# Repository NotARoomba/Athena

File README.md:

<h1 align="center">
  <br>
  
  <br>
  Athena
  <br>
</h1>

<h4 align="center">
Advanced Flight Computer with Triple MCU Architecture

</h4>

<div align="center">

</div>

<p align="center">
  <a href="#key-features">Key Features</a> •
  <a href="#board-overview">Board Overview</a> •
  <a href="#specifications">Specifications</a> •
  <a href="#components">Components</a> •
  <a href="#credits">Credits</a> •
  <a href="#license">License</a>
</p>

## Key Features

- **Triple MCU Architecture**: STM32H753VIT6 (MPU), STM32H743VIT6 (TPU), STM32G474RET6 (SPU)
- **6 Pyro Channels**: Direct 12V battery connection with fuse protection
- **6 PWM Channels**: 2 for TVC (Thrust Vector Control), 4 for fin control
- **Advanced Sensors**: Triple ICM-45686 IMUs, LIS2MDLTR magnetometer, ICP-20100 & BMP388 barometers
- **GNSS & Communication**: NEO-M8U-06B GPS, LoRa RA-02 telemetry, Bluetooth DA14531MOD
- **Storage**: SD Card + Winbond W25Q256JV flash memory
- **Power Management**: 7.4-12V LiPo battery with BQ25713 charger, TPS25751 USB-C PD controller
- **6-Layer PCB**: Dedicated power planes and signal routing

## Board Overview

Athena is a high-performance flight computer designed for advanced rocketry applications. The board features a sophisticated 6-layer PCB design with dedicated power planes and optimized signal routing.

### Board Images

### PCB Design Process

The board was designed in EasyEDA with careful attention to power distribution and signal integrity:

## Specifications

### Physical Specifications

- **Board Size**: 80mm × 140mm
- **Layer Count**: 6 layers
- **Thickness**: Standard PCB thickness
- **Connectors**: USB-C, SD Card slot, various headers

### Power Specifications

- **Input Voltage**: 7.4V LiPo battery
- **Regulated Outputs**: 5V, 3.3V
- **Charging**: USB-C Power Delivery support

### Communication Interfaces

- **GNSS**: NEO-M8U-06B GPS module
- **LoRa**: RA-02 for long-range telemetry
- **Bluetooth**: DA14531MOD for local communication
- **CAN**: TCAN1057AVDRQ1 transceiver
- **USB**: TUSB2036 USB hub
- **UART**: Dedicated UART channels for each STM with ESD protection

## Components

### Microcontrollers

- **MPU (Main Processing Unit)**: STM32H753VIT6 - Handles sensors and Kalman filtering
- **TPU (Telemetry Processing Unit)**: STM32H743VIT6 - Manages LoRa, SD card, and flash memory
- **SPU (Servo Processing Unit)**: STM32G474RET6 - Controls pyro channels and PWM outputs

### Sensors

- **IMU**: 3× ICM-45686 (triple redundancy)
- **Magnetometer**: LIS2MDLTR
- **Barometers**: ICP-20100, BMP388 (dual redundancy)

### Power Management

- **Battery Charger**: BQ25713RSNR (on the TPS25751's I2C controller bus)
- **USB-C PD Controller**: TPS25751DREFR (patched over I2C by the SPU at power-up)
- **Buck Converters**: LM5145RGYR (servo), TPS5430 (3.3V)

### Storage & Communication

- **Flash Memory**: Winbond W25Q256JV
- **SD Card**: Standard microSD slot
- **GPS**: NEO-M8U-06B
- **LoRa**: RA-02
- **Bluetooth**: DA14531MOD-00F01002

## Dashboard

[docs/](docs/) is the built dashboard (source in [software/web](software/web): React 19 + Vite +
Tailwind + recharts + three.js, same stack as [cyberboard.notaroomba.dev](https://cyberboard.notaroomba.dev)),
served at [athena.notaroomba.dev](https://athena.notaroomba.dev) by GitHub Pages. It shows the 3D
attitude, accel/gyro/altitude charts, flight flags, GPS, a live **ground-track map** (filter
estimate, dead-reckoned stretches dashed, raw GPS, landing estimate from the current descent,
distance/bearing from the pad, apogee and max speed), and the SPU **recovery & power** panel
(flight phase, arming, the six pyro channels, battery/charger/USB-PD state) with ARM / DISARM /
FIRE / servo / main-altitude commands when a writable link is open, a **flight event timeline**
(launch, phases, pyro firings, arming) with a summary line (apogee, max speed, max g, flight time,
landing distance), per-type frame rates, a **REC** button that saves the raw link stream as a
replayable `.bin`, a **REPORT** button that downloads a JSON flight report (summary, events, tracks, last
frames, console), a **pre-flight checklist** (GO/NO-GO read from the live data: IMUs, baro, GPS fix,
pad origin, SPU link, main altitude, radio, arming, plus a hand-ticked list), **SOUND** alerts on
launch/apogee/pyro/landing, a **T-60 countdown** (beeps over the last 10 s, cancels itself at launch), a no-data
banner, the altitude and phase in the tab title, a metres/feet display toggle, and keyboard shortcuts (`d` demo, `t` countdown, `c` checklist,
`s` sound, `l` login, `r` record). Data sources:

- **SERIAL**: any of the three USB ports (WebSerial, Chrome/Edge over https or localhost).
- **BLUETOOTH**: the DA14531 on the TPU over Web Bluetooth (DSPS serial-bridge firmware streams the
  telemetry; the factory CodeLess firmware only answers AT commands).
- **REPLAY**: an `ATHnnnnn.BIN` from the SD card, a flash dump, a dashboard recording or a ground-station
  log, paced by its own timestamps, with a speed selector, pause (space) and a seek bar.
- **DEMO**: a scripted flight (with a GPS dropout) through the real encoder/decoder.
- viewers: an admin's serial/Bluetooth bytes (or a ground station's) are relayed through the WebSocket
  server in [software/server](software/server) (axum, on Railway at `api.athena.notaroomba.dev`). A logged-in
  viewer can also send commands: the server hands them to the connected ground station, which writes them
  to its uplink port, and reports whether anyone was there to carry them.

Locally: `cd software/web && npm install && npm run dev` (or `python3 -m http.server 8787 --directory docs`).

## Firmware

Three CubeMX projects (`firmware/MPU`, `firmware/TPU`, `firmware/SPU`) share the pure-C
modules in `firmware/Athena`: the inter-MCU/LoRa framing (`athena_link`), the UBX parser
(`ubx`), the navigation filter (`fusion`: Mahony attitude + per-axis Kalman filters with
IMU dead reckoning, barometer and GPS corrections) and the SPU recovery logic (`recovery`:
flight phase from the fused state, drogue at apogee, main below a set altitude, servo outputs).
`cd firmware && make debug` builds all three (`brew install osx-cross/arm/arm-gcc-bin@14` for the
toolchain) and `make host-test` runs the PC self-check of the shared modules including a scripted
flight through the recovery logic.

`./firmware/flash.sh` flashes over USB DFU with `dfu-util` and tells the MCUs apart by USB hub
port. No buttons are needed: `B` on any MCU's USB console disconnects USB, leaves a magic word in
RAM and resets into the ST ROM bootloader (`J` jumps in place as a fallback); the script does this
itself. After reset each MCU shows its identity colour for 3 s: **MPU green, TPU red, SPU blue**.

Links: MPU -> TPU (UART4/UART8, state 20 Hz, GPS back), MPU -> SPU (UART8/UART5, state 20 Hz,
SPU status 2 Hz back), TPU -> MPU -> SPU for commands (LoRa uplink, USB, Bluetooth). The TPU
logs every link frame to the microSD card (one `ATHnnnnn.BIN` per boot, card hot-plug safe) and
to the W25Q256 flash, sends telemetry + SPU status over LoRa and over UART7 to the Bluetooth module;
`tools/athlog.py` dumps the flash log over USB and converts logs to CSV.

**Ground station on an RTL-SDR** (`tools/lora_rx.py`, macOS/Linux/Windows): a complete LoRa receiver for
the downlink (SF7, 125 kHz, sync 0x12) written in numpy, no GNU Radio, about 15% of one core at the
dongle's native 1 MS/s. It decodes the Athena frames straight from the IQ stream (the frames' own CRCs
verified 92% of packets on the bench), logs them to a replayable `athena-lora-*.bin`, and by default opens
the web dashboard fed live by this process (it serves `docs/` and speaks the relay protocol on
`ws://localhost:3001/ws`, including a `station` message with signal level, carrier offset and packet
counts that the dashboard shows in its footer, and its own log lines as TEXT frames so they appear in the
dashboard console; through `--relay` the public site gets both as well). `--app` opens it as a desktop window (pywebview) instead of
a browser tab, `--gain auto` uses the tuner AGC (the dongle is retried every 3 s when busy or unplugged),
`--uplink /dev/tty...` adds a command path (the rocket's USB console on the bench, or a TPU
in ground-station mode: `G` on its console turns a second board into a LoRa<->USB relay), `--tui` gives a
terminal UI, `--relay wss://api.athena.notaroomba.dev/ws --password ...` also feeds the public site and
accepts commands from it, `--file cap.cu8` replays a capture. Needs `pip install numpy scipy websockets
websocket-client pyserial pywebview` and `rtl_sdr` (`brew install librtlsdr`). `tools/build_station.sh` packs
it into one standalone executable (`dist/station/athena-station`, PyInstaller, dashboard files included) so a
laptop at the range only needs `rtl_sdr` installed; the `station` GitHub Actions workflow builds it for
macOS, Windows and Linux (run it from the Actions tab or push a `v*` tag, then download the artifact).
`tools/lora_check.py` is the quick PHY check (burst period,
preamble, sync word).

USB console characters: all MCUs `B`/`J` (DFU), `L` LEDs off/on; TPU `D` dump flash log, `E` restart it,
`S` sync SD, `F` format SD, `G` ground-station mode (persistent); SPU `A` arm, `d` disarm, `1`-`6` fire a
channel (armed only), `s` sweep servo 1, `r` reset the MPU. Pyros only get power when the external ARM terminal is closed.

## Credits

This project uses:

- [EasyEDA](https://easyeda.com/) - PCB design and schematic capture
- [STM32 HAL](https://www.st.com/en/embedded-software/stm32cube-hal.html) - Hardware abstraction layer
- [JLCPCB](https://jlcpcb.com/) - PCB manufacturing and assembly
- [Figma](https://figma.com/) - Silkscreen design

## You may also like...

- [Niveles De Niveles](https://github.com/NotARoomba/NivelesDeNiveles) – Real-time flood alert app
- [Linea](https://github.com/NotARoomba/Linea) – An EMR tablet
- [Tamaki](https://github.com/NotARoomba/Tamaki) – A cute HackPad

## License

MIT

---

> [notaroomba.dev](https://notaroomba.dev) &nbsp;&middot;&nbsp;
> GitHub [@NotARoomba](https://github.com/NotARoomba)

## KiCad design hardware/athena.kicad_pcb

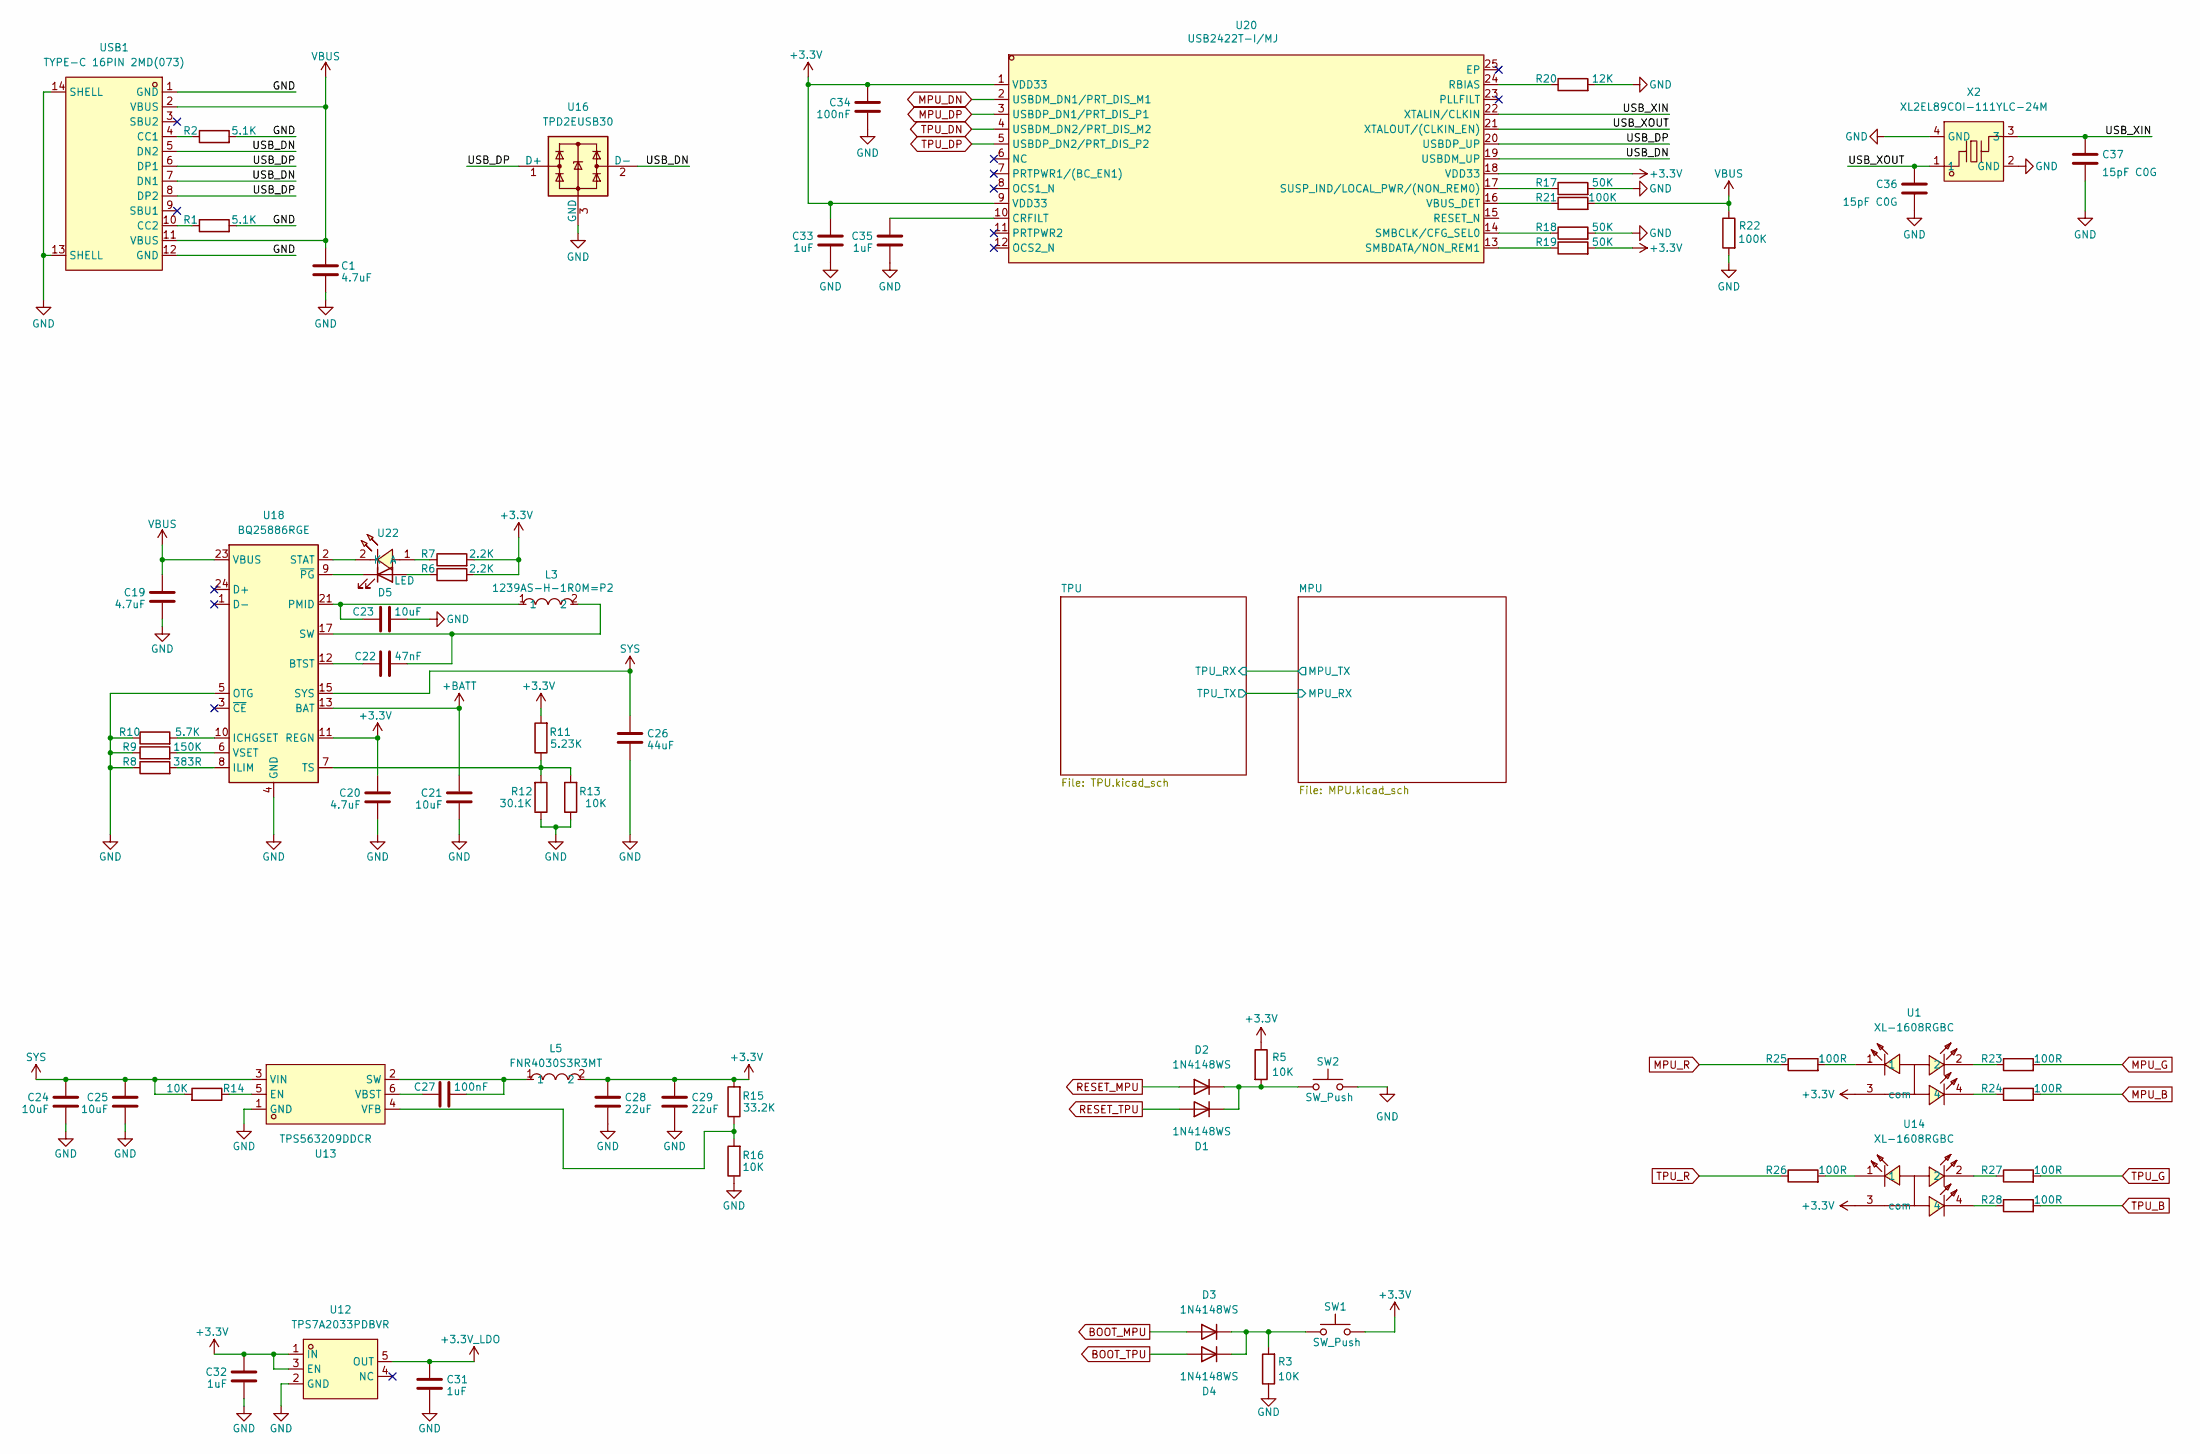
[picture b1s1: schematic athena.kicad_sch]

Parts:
C1, C19, C20: 4.7uF; C_0603_1608Metric
C21, C23, C24, C25: 10uF; C_0603_1608Metric
C22: 47nF; C_0402_1005Metric
C26: 44uF; C_0805_2012Metric
C27: 100nF; C_0402_1005Metric
C28, C29: 22uF; C_0805_2012Metric
C31, C32, C33, C35: 1uF; C_0402_1005Metric_Pad0.74x0.62mm_HandSolder
C34: 100nF; C_0402_1005Metric_Pad0.74x0.62mm_HandSolder
C36, C37: 15pF C0G; C_0402_1005Metric_Pad0.74x0.62mm_HandSolder
D1, D2, D3, D4: 1N4148WS; D_SOD-323
D5: LED; LED_0402_1005Metric; LCSC C52125197
L3: 1239AS-H-1R0M=P2; L1008; MPN 1239AS-H-1R0M=P2; LCSC Part C167447
L5: FNR4030S3R3MT; IND-SMD_L4.0-W4.0_FNR40XXS; MPN FNR4030S3R3MT; LCSC Part C167870
R1, R2: 5.1K; R_0402_1005Metric
R3, R5, R13, R14, R16: 10K; R_0402_1005Metric
R6, R7: 2.2K; R_0402_1005Metric
R8: 383R; R_0402_1005Metric
R9: 150K; R_0402_1005Metric
R10: 5.7K; R_0402_1005Metric
R11: 5.23K; R_0402_1005Metric
R12: 30.1K; R_0402_1005Metric
R15: 33.2K; R_0402_1005Metric
R17, R18, R19: 50K; R_0402_1005Metric
R20: 12K; R_0402_1005Metric
R21, R22: 100K; R_0402_1005Metric
R23, R24, R25, R26, R27, R28: 100R; R_0402_1005Metric
SW1, SW2: SW_Push; SW-SMD_L3.9-W3.0-P4.45; LCSC C720477
U1, U14: XL-1608RGBC; LED-SMD_4P-L1.6-W0.8-BL; MPN XL-1608RGBC; LCSC Part C5349936
U12: TPS7A2033PDBVR; SOT-23-5_L2.9-W1.6-P0.95-LS2.8-BR; LCSC Part C2862740
U13: TPS563209DDCR; SOT-23-6_L2.9-W1.6-P0.95-LS2.8-BR; LCSC Part C181974
U16: TPD2EUSB30; Texas_DRT-3
U18: BQ25886RGE; Texas_RGE0024H_VQFN-24-1EP_4x4mm_P0.5mm_EP2.7x2.7mm
U20: USB2422T-I/MJ; QFN-24_L4.0-W4.0-P0.50-TL-EP2.5; LCSC Part C622610
U22: SZYY0402Y_C434450; LED0402-FD_YELLOW; LCSC Part C434450
USB1: TYPE-C 16PIN 2MD(073); USB-C-SMD_TYPE-C-6PIN-2MD-073; LCSC Part C2765186
X2: XL2EL89COI-111YLC-24M; CRYSTAL-SMD_4P-L3.2-W2.5-BL; MPN XL2EL89COI-111YLC-24M; LCSC Part C5444545

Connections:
+3.3V: C20.1, C28.1, C29.1, C32.1, C33.1, C34.1, L5.2, R5.1, R6.2, R7.2, R11.2, R15.2, R19.2, SW1.2, U1.3 (com), U12.1 (IN), U12.3 (EN), U14.3 (com), U18.11 (REGN), U20.1 (VDD33), U20.9 (VDD33), U20.18 (VDD33); also elsewhere on the board
+3.3V_LDO: C31.1, U12.5 (OUT); also elsewhere on the board
+BATT: C21.1, U18.13 (BAT), U18.14 (BAT)
/USB_DN: U16.2 (D-), U20.19 (USBDM_UP), USB1.5 (DN2), USB1.7 (DN1)
/USB_DP: U16.1 (D+), U20.20 (USBDP_UP), USB1.6 (DP1), USB1.8 (DP2)
/USB_XIN: C37.1, U20.22 (XTALIN/CLKIN), X2.3
/USB_XOUT: C36.1, U20.21 (XTALOUT/(CLKIN_EN)), X2.1
BOOT_MPU: D3.2 (A); also elsewhere on the board
BOOT_TPU: D4.2 (A); also elsewhere on the board
GND: C1.2, C19.2, C20.2, C21.2, C23.2, C24.2, C25.2, C26.2, C28.2, C29.2, C31.2, C32.2, C33.2, C34.2, C35.2, C36.2, C37.2, R1.2, R2.2, R3.1, R8.1, R9.1, R10.1, R12.1, R13.1, R16.1, R17.2, R18.2, R20.2, R22.2, SW2.2, U12.2 (GND), U13.1 (GND), U16.3 (GND), U18.4 (GND), U18.5 (OTG), U18.19 (GND), U18.20 (GND), U18.25 (GND), USB1.1 (GND), USB1.12 (GND), USB1.13 (SHELL), USB1.14 (SHELL), X2.2 (GND), X2.4 (GND); also elsewhere on the board
MPU_B: R24.2; also elsewhere on the board
MPU_DN: U20.2 (USBDM_DN1/PRT_DIS_M1); also elsewhere on the board
MPU_DP: U20.3 (USBDP_DN1/PRT_DIS_P1); also elsewhere on the board
MPU_G: R23.2; also elsewhere on the board
MPU_R: R25.1; also elsewhere on the board
unnamed: C22.1, L3.2, U18.17 (SW), U18.18 (SW)
unnamed: C23.1, L3.1, U18.21 (PMID), U18.22 (PMID)
unnamed: D1.1 (K), D2.1 (K), R5.2, SW2.1
unnamed: D3.1 (K), D4.1 (K), R3.2, SW1.1
unnamed: D5.2 (A), R6.1
unnamed: D5.1 (K), U18.9 (~PG)
unnamed: R23.1, U1.2
unnamed: R24.1, U1.4
unnamed: R25.2, U1.1
unnamed: R26.2, U14.1
unnamed: R27.1, U14.2
unnamed: R28.1, U14.4
unnamed: R14.1, U13.5 (EN)
unnamed: C27.1, L5.1, U13.2 (SW)
unnamed: C27.2, U13.6 (VBST)
unnamed: R15.1, R16.2, U13.4 (VFB)
unnamed: C22.2, U18.12 (BTST)
unnamed: R10.2, U18.10 (ICHGSET)
unnamed: R8.2, U18.8 (ILIM)
unnamed: U18.2 (STAT), U22.2 (K)
unnamed: R11.1, R12.2, R13.2, U18.7 (TS)
unnamed: R9.2, U18.6 (VSET)
unnamed: C35.1, U20.10 (CRFILT)
unnamed: R20.1, U20.24 (RBIAS)
unnamed: R18.1, U20.14 (SMBCLK/CFG_SEL0)
unnamed: R19.1, U20.13 (SMBDATA/NON_REM1)
unnamed: R17.1, U20.17 (SUSP_IND/LOCAL_PWR/(NON_REM0))
unnamed: R21.1, U20.16 (VBUS_DET)
unnamed: R7.1, U22.1 (A)
unnamed: R2.1, USB1.4 (CC1)
unnamed: R1.1, USB1.10 (CC2)
RESET_MPU: D2.2 (A); also elsewhere on the board
RESET_TPU: D1.2 (A); also elsewhere on the board
SYS: C24.1, C25.1, C26.1, R14.2, U13.3 (VIN), U18.15 (SYS), U18.16 (SYS)
TPU_B: R28.2; also elsewhere on the board
TPU_DN: U20.4 (USBDM_DN2/PRT_DIS_M2); also elsewhere on the board
TPU_DP: U20.5 (USBDP_DN2/PRT_DIS_P2); also elsewhere on the board
TPU_G: R27.2; also elsewhere on the board
TPU_R: R26.1; also elsewhere on the board
VBUS: C1.1, C19.1, R21.2, R22.1, U18.23 (VBUS), USB1.2 (VBUS), USB1.11 (VBUS)

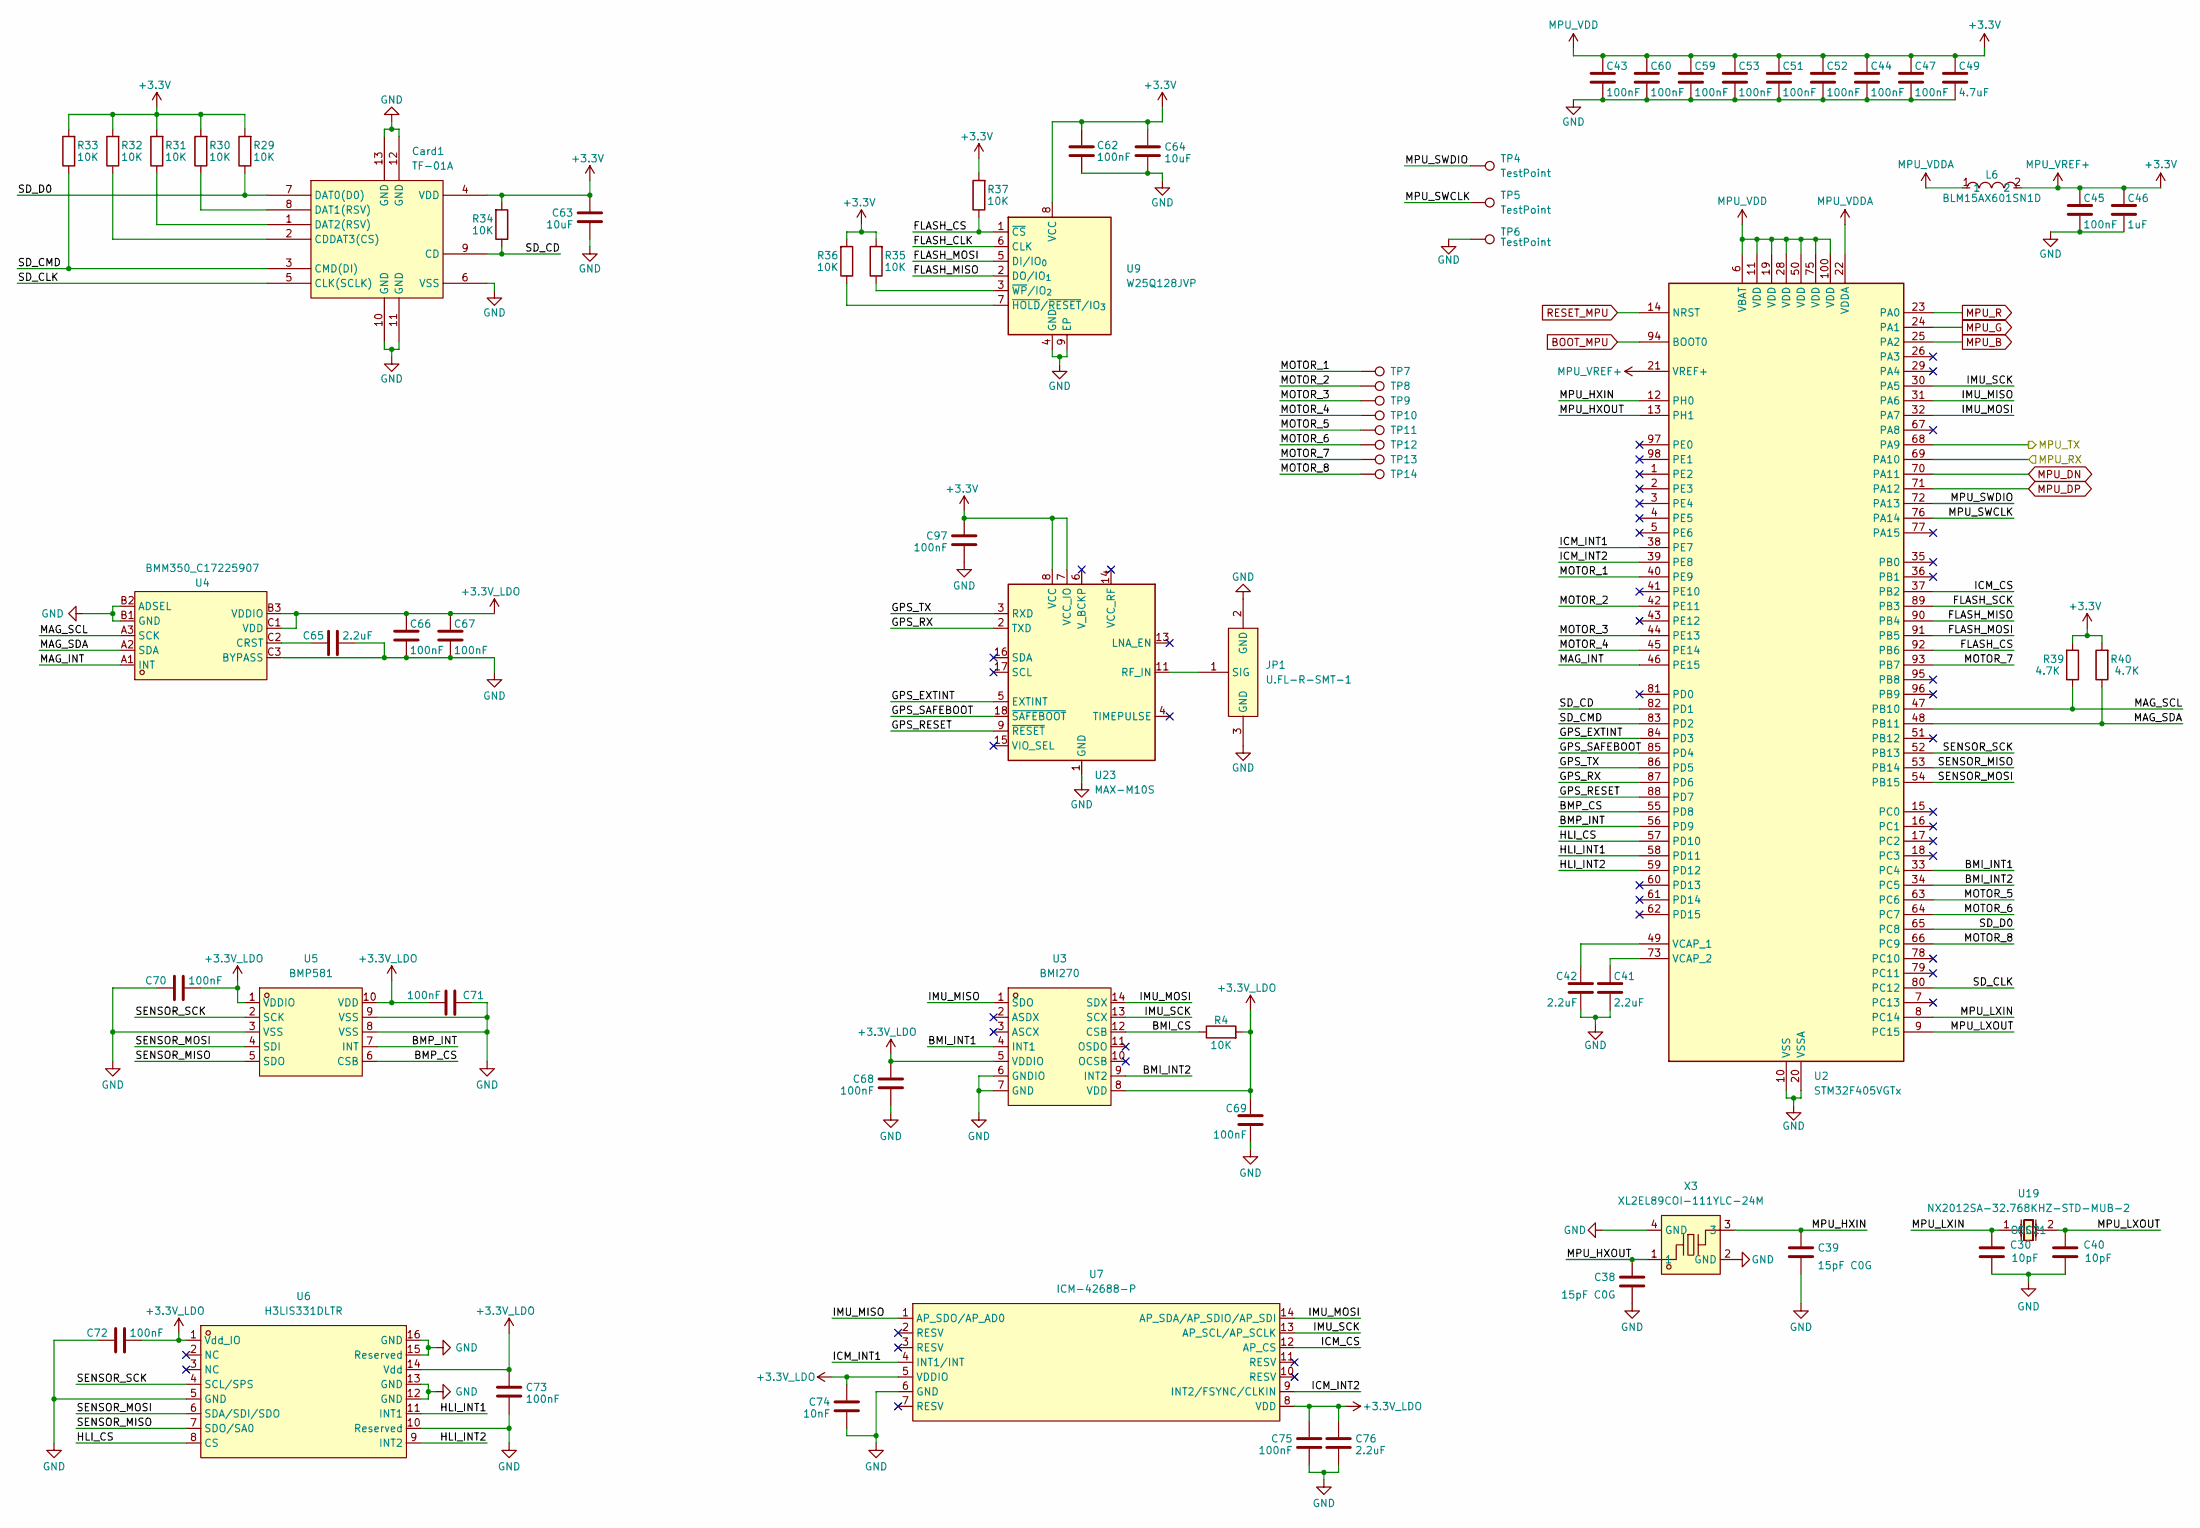
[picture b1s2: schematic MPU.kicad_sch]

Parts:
C30, C40: 10pF; C_0402_1005Metric
C38, C39: 15pF C0G; C_0402_1005Metric_Pad0.74x0.62mm_HandSolder
C41, C42, C65, C76: 2.2uF; C_0402_1005Metric
C43, C44, C45, C47, C51, C52, C53, C59, C60, C62, C66, C67, C68, C69, C70, C71, C72, C73, C75, C97: 100nF; C_0402_1005Metric
C46: 1uF; C_0402_1005Metric
C49: 4.7uF; C_0603_1608Metric
C63, C64: 10uF; C_0603_1608Metric
C74: 10nF; C_0402_1005Metric
Card1: TF-01A; TF-SMD_TF-01A; LCSC Part C91145
JP1: U.FL-R-SMT-1; RF-SMD_FRF05002-JSS103M; MPN U.FL-R-SMT-1(80); LCSC Part C88374
L6: BLM15AX601SN1D; L0402; MPN BLM15AX601SN1D; LCSC Part C76886
R4, R29, R30, R31, R32, R33, R34, R35, R36, R37: 10K; R_0402_1005Metric
R39, R40: 4.7K; R_0402_1005Metric
TP4, TP5, TP6: TestPoint; TestPoint_Pad_1.0x1.0mm
TP7, TP8, TP9, TP10, TP11, TP12, TP13, TP14: TestPoint; TestPoint_Pill
U2: STM32F405VGTx; LQFP-100_14x14mm_P0.5mm
U3: BMI270; LGA-14_L3.0-W2.5-P0.50-BR; LCSC Part C2836813
U4: BMM350_C17225907; WLCSP-9_L1.3-W1.3-R3-C3-P0.40-TL; LCSC Part C17225907
U5: BMP581; LGA-10_L2.0-W2.0-P0.50-TL_BMP581; LCSC Part C5362283
U6: H3LIS331DLTR; LGA-16_L3.0-W3.0-P0.50-BL; LCSC Part C2655074
U7: ICM-42688-P; LGA-14_L3.0-W2.5-P0.50-TL; LCSC Part C1850418
U9: W25Q128JVP; WSON-8-1EP_6x5mm_P1.27mm_EP3.4x4.3mm
U19: NX2012SA-32.768KHZ-STD-MUB-2; CRYSTAL-SMD_L2.0-W1.2; LCSC Part C891748
U23: MAX-M10S; ublox_MAX
X3: XL2EL89COI-111YLC-24M; CRYSTAL-SMD_4P-L3.2-W2.5-BL; MPN XL2EL89COI-111YLC-24M; LCSC Part C5444545

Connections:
+3.3V: C43.1, C44.1, C45.1, C46.1, C47.1, C49.1, C51.1, C52.1, C53.1, C59.1, C60.1, C62.1, C63.1, C64.1, C97.1, Card1.4 (VDD), L6.2, R29.2, R30.2, R31.2, R32.2, R33.2, R34.2, R35.2, R36.2, R37.2, R39.2, R40.2, U2.6 (VBAT), U2.11 (VDD), U2.19 (VDD), U2.21 (VREF+), U2.28 (VDD), U2.50 (VDD), U2.75 (VDD), U2.100 (VDD), U9.8 (VCC), U23.7 (VCC_IO), U23.8 (VCC); also elsewhere on the board
+3.3V_LDO: C66.1, C67.1, C68.1, C69.1, C70.2, C71.2, C72.2, C73.1, C74.1, C75.1, C76.1, R4.2, U3.5 (VDDIO), U3.8 (VDD), U4.B3 (VDDIO), U4.C1 (VDD), U5.1 (VDDIO), U5.10 (VDD), U6.1 (Vdd_IO), U6.14 (Vdd), U7.5 (VDDIO), U7.8 (VDD); also elsewhere on the board
/MPU/BMI_CS: R4.1, U3.12 (CSB)
/MPU/BMI_INT1: U2.33 (PC4), U3.4 (INT1)
/MPU/BMI_INT2: U2.34 (PC5), U3.9 (INT2)
/MPU/BMP_CS: U2.55 (PD8), U5.6 (CSB)
/MPU/BMP_INT: U2.56 (PD9), U5.7 (INT)
/MPU/FLASH_CLK: U9.6 (CLK)
/MPU/FLASH_CS: R37.1, U2.92 (PB6), U9.1 (~CS)
/MPU/FLASH_MISO: U2.90 (PB4), U9.2 (DO/IO_{1})
/MPU/FLASH_MOSI: U2.91 (PB5), U9.5 (DI/IO_{0})
/MPU/FLASH_SCK: U2.89 (PB3)
/MPU/GPS_EXTINT: U2.84 (PD3), U23.5 (EXTINT)
/MPU/GPS_RESET: U2.88 (PD7), U23.9 (~RESET)
/MPU/GPS_RX: U2.87 (PD6), U23.2 (TXD)
/MPU/GPS_SAFEBOOT: U2.85 (PD4), U23.18 (~SAFEBOOT)
/MPU/GPS_TX: U2.86 (PD5), U23.3 (RXD)
/MPU/HLI_CS: U2.57 (PD10), U6.8 (CS)
/MPU/HLI_INT1: U2.58 (PD11), U6.11 (INT1)
/MPU/HLI_INT2: U2.59 (PD12), U6.9 (INT2)
/MPU/ICM_CS: U2.37 (PB2), U7.12 (AP_CS)
/MPU/ICM_INT1: U2.38 (PE7), U7.4 (INT1/INT)
/MPU/ICM_INT2: U2.39 (PE8), U7.9 (INT2/FSYNC/CLKIN)
/MPU/IMU_MISO: U2.31 (PA6), U3.1 (SDO), U7.1 (AP_SDO/AP_AD0)
/MPU/IMU_MOSI: U2.32 (PA7), U3.14 (SDX), U7.14 (AP_SDA/AP_SDIO/AP_SDI)
/MPU/IMU_SCK: U2.30 (PA5), U3.13 (SCX), U7.13 (AP_SCL/AP_SCLK)
/MPU/MAG_INT: U2.46 (PE15), U4.A1 (INT)
/MPU/MAG_SCL: R39.1, U2.47 (PB10), U4.A3 (SCK)
/MPU/MAG_SDA: R40.1, U2.48 (PB11), U4.A2 (SDA)
/MPU/MOTOR_1: TP7.1 (1_1), U2.40 (PE9)
/MPU/MOTOR_2: TP8.1 (1_1), U2.42 (PE11)
/MPU/MOTOR_3: TP9.1 (1_1), U2.44 (PE13)
/MPU/MOTOR_4: TP10.1 (1_1), U2.45 (PE14)
/MPU/MOTOR_5: TP11.1 (1_1), U2.63 (PC6)
/MPU/MOTOR_6: TP12.1 (1_1), U2.64 (PC7)
/MPU/MOTOR_7: TP13.1 (1_1), U2.93 (PB7)
/MPU/MOTOR_8: TP14.1 (1_1), U2.66 (PC9)
/MPU/MPU_HXIN: C39.1, U2.12 (PH0), X3.3
/MPU/MPU_HXOUT: C38.1, U2.13 (PH1), X3.1
/MPU/MPU_LXIN: C30.1, U2.8 (PC14), U19.1 (OSC1)
/MPU/MPU_LXOUT: C40.1, U2.9 (PC15), U19.2 (OSC2)
/MPU/MPU_RX: U2.69 (PA10); also elsewhere on the board
/MPU/MPU_SWCLK: TP5.1 (1_1), U2.76 (PA14)
/MPU/MPU_SWDIO: TP4.1 (1_1), U2.72 (PA13)
/MPU/MPU_TX: U2.68 (PA9); also elsewhere on the board
/MPU/SD_CD: Card1.9 (CD), R34.1, U2.82 (PD1)
/MPU/SD_CLK: Card1.5 (CLK(SCLK)), U2.80 (PC12)
/MPU/SD_CMD: Card1.3 (CMD(DI)), R33.1, U2.83 (PD2)
/MPU/SD_D0: Card1.7 (DAT0(D0)), R29.1, U2.65 (PC8)
/MPU/SENSOR_MISO: U2.53 (PB14), U5.5 (SDO), U6.7 (SDO/SA0)
/MPU/SENSOR_MOSI: U2.54 (PB15), U5.4 (SDI), U6.6 (SDA/SDI/SDO)
/MPU/SENSOR_SCK: U2.52 (PB13), U5.2 (SCK), U6.4 (SCL/SPS)
BOOT_MPU: U2.94 (BOOT0); also elsewhere on the board
GND: C30.2, C38.2, C39.2, C40.2, C41.2, C42.2, C43.2, C44.2, C45.2, C46.2, C47.2, C49.2, C51.2, C52.2, C53.2, C59.2, C60.2, C62.2, C63.2, C64.2, C65.1, C66.2, C67.2, C68.2, C69.2, C70.1, C71.1, C72.1, C73.2, C74.2, C75.2, C76.2, C97.2, Card1.6 (VSS), Card1.10 (GND), Card1.11 (GND), Card1.12 (GND), Card1.13 (GND), JP1.2 (GND), JP1.3 (GND), TP6.1 (1_1), U2.10 (VSS), U2.20 (VSSA), U2.27 (VSS), U2.74 (VSS), U2.99 (VSS), U3.6 (GNDIO), U3.7 (GND), U4.B1 (GND), U4.B2 (ADSEL), U4.C3 (BYPASS), U5.3 (VSS), U5.8 (VSS), U5.9 (VSS), U6.5 (GND), U6.10 (Reserved), U6.12 (GND), U6.13 (GND), U6.15 (Reserved), U6.16 (GND), U7.6 (GND), U9.4 (GND), U9.9 (EP), U23.1 (GND), U23.10 (GND), U23.12 (GND), X3.2 (GND), X3.4 (GND); also elsewhere on the board
MPU_B: U2.25 (PA2); also elsewhere on the board
MPU_DN: U2.70 (PA11); also elsewhere on the board
MPU_DP: U2.71 (PA12); also elsewhere on the board
MPU_G: U2.24 (PA1); also elsewhere on the board
MPU_R: U2.23 (PA0); also elsewhere on the board
MPU_VDDA: L6.1, U2.22 (VDDA)
unnamed: Card1.2 (CDDAT3(CS)), R32.1
unnamed: Card1.8 (DAT1(RSV)), R30.1
unnamed: Card1.1 (DAT2(RSV)), R31.1
unnamed: JP1.1 (SIG), U23.11 (RF_IN)
unnamed: C42.1, U2.49 (VCAP_1)
unnamed: C41.1, U2.73 (VCAP_2)
unnamed: C65.2, U4.C2 (CRST)
unnamed: R36.1, U9.7 (~HOLD/~RESET/IO_{3})
unnamed: R35.1, U9.3 (~WP/IO_{2})
RESET_MPU: U2.14 (NRST); also elsewhere on the board

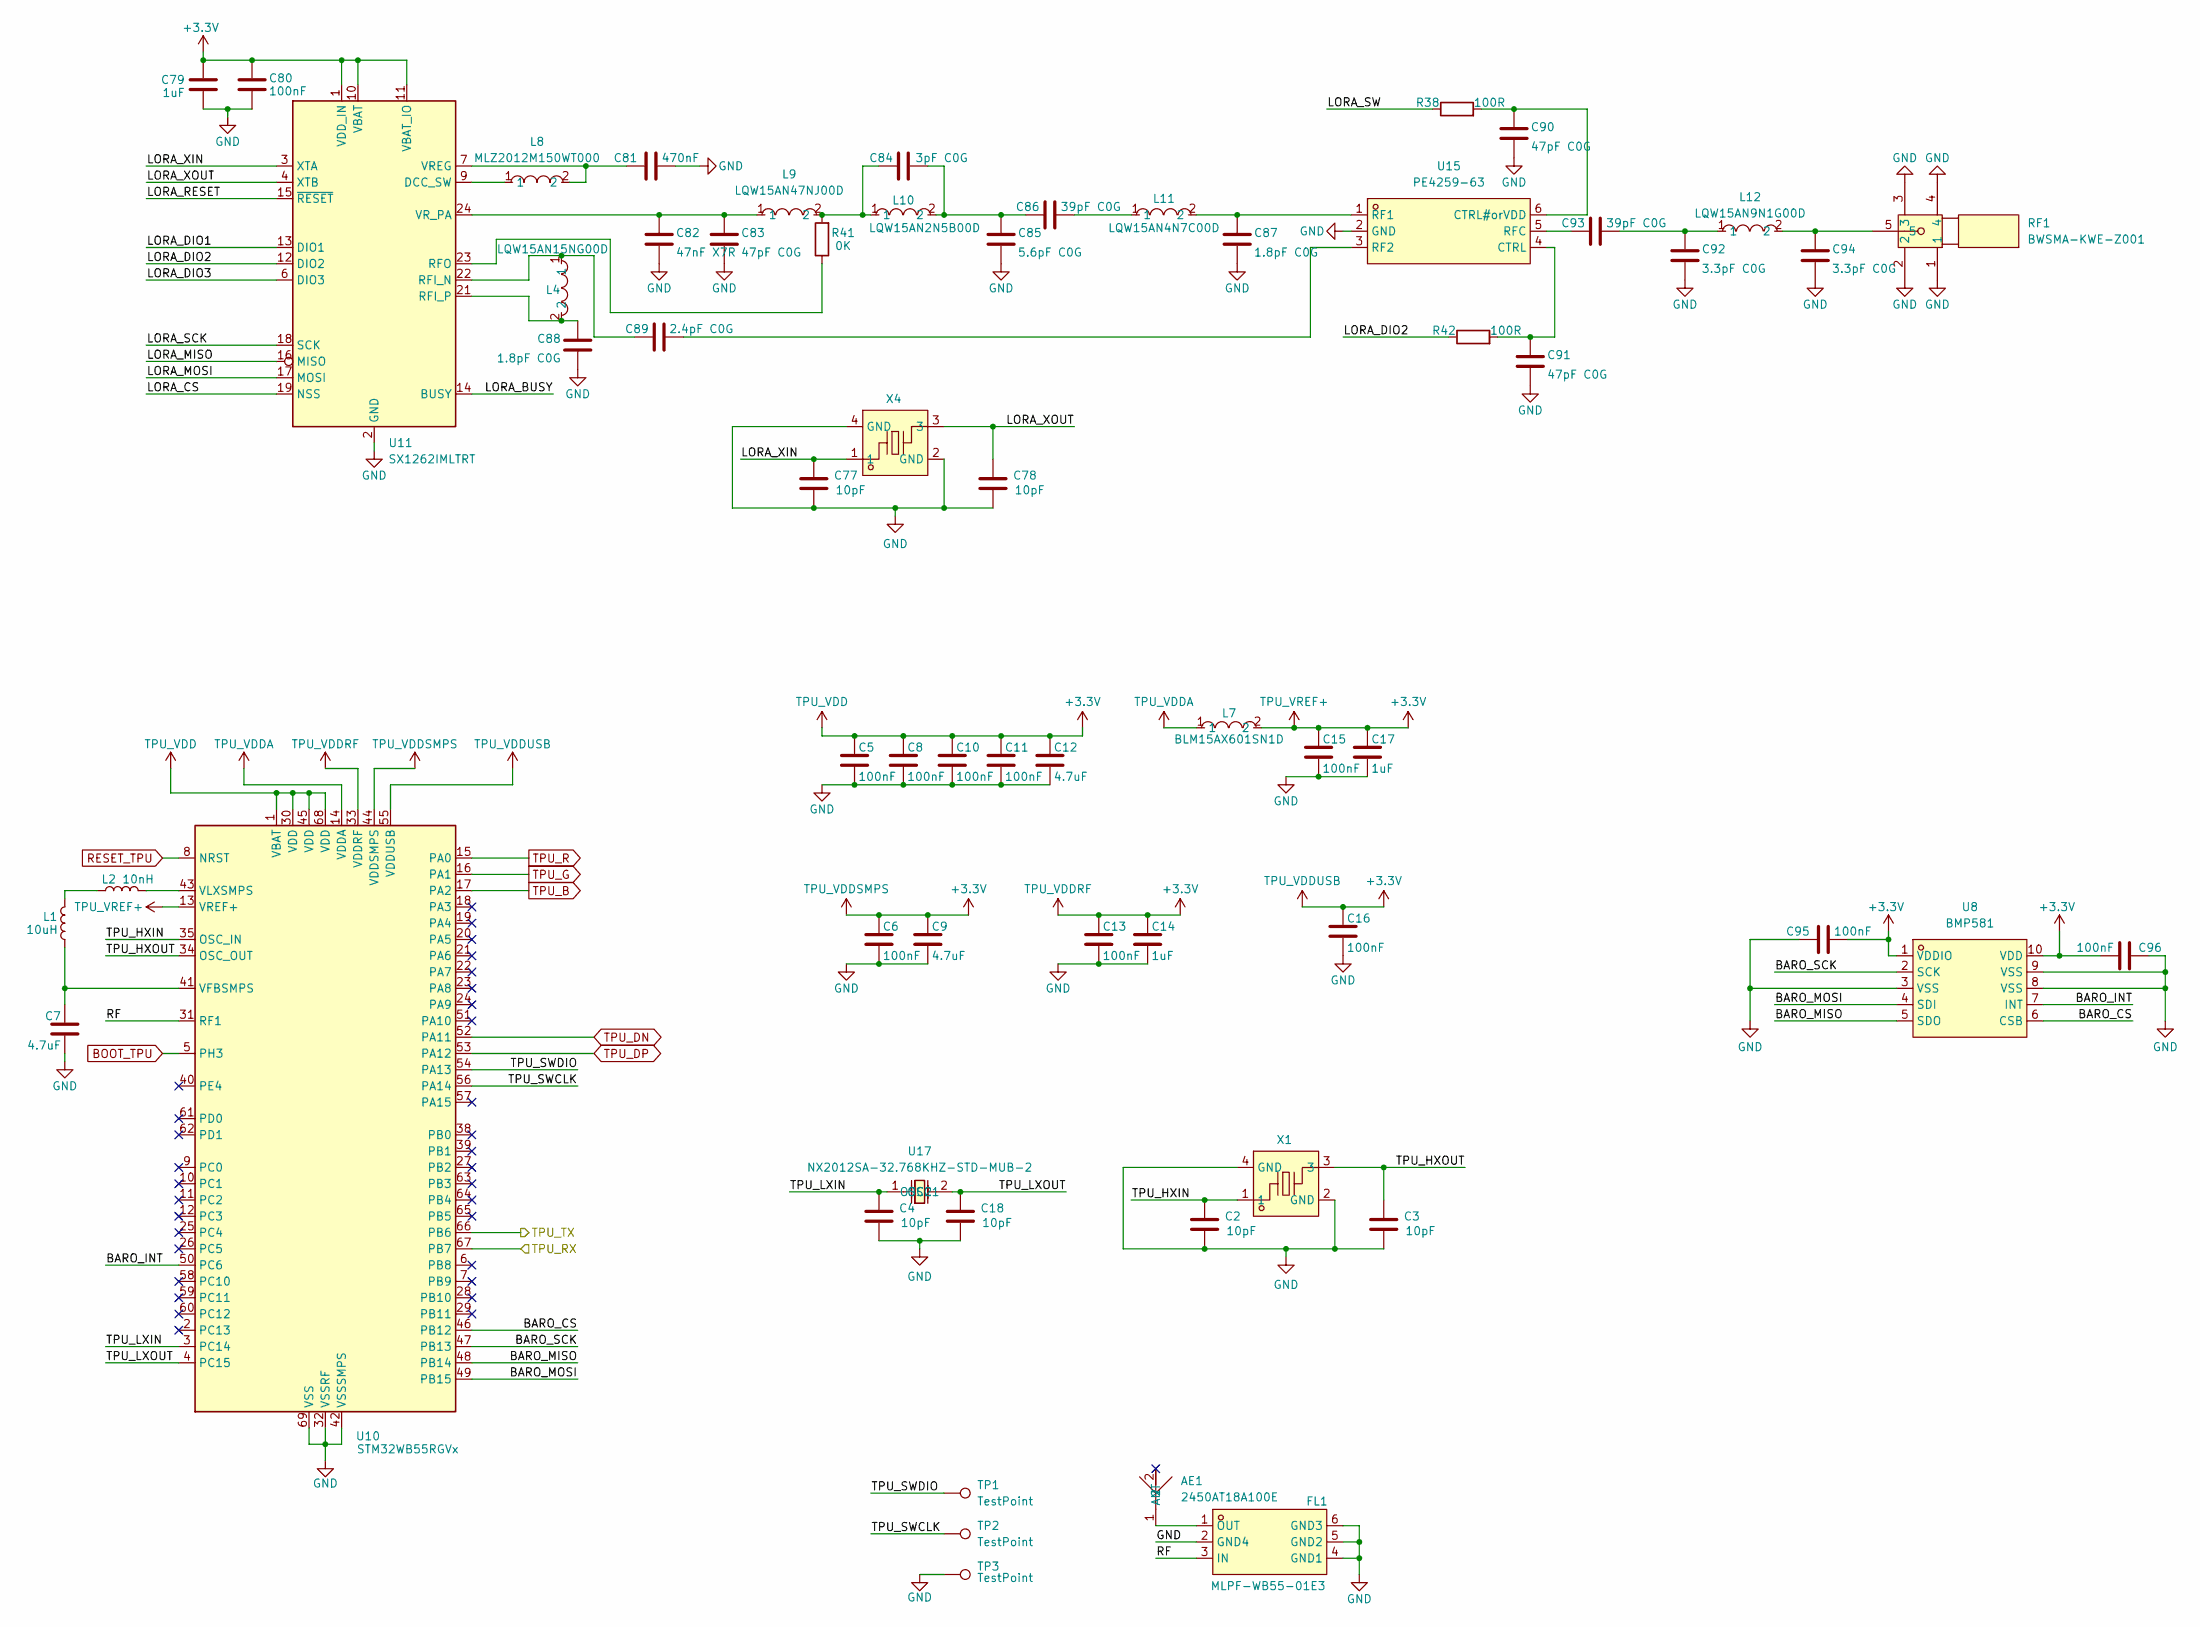
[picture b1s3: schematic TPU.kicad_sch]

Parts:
AE1: 2450AT18A100E; ANT-SMD_L3.2-W1.6; LCSC Part C89334
C2, C3, C4, C18, C77, C78: 10pF; C_0402_1005Metric
C5, C6, C8, C10, C11, C13, C15, C16, C80, C95, C96: 100nF; C_0402_1005Metric
C7, C9, C12: 4.7uF; C_0603_1608Metric
C14, C17: 1uF; C_0402_1005Metric
C79: 1uF; C_0402_1005Metric_Pad0.74x0.62mm_HandSolder
C81: 470nF; C_0402_1005Metric
C82: 47nF X7R; C_0402_1005Metric
C83, C90, C91: 47pF C0G; C_0402_1005Metric
C84: 3pF C0G; C_0402_1005Metric
C85: 5.6pF C0G; C_0402_1005Metric
C86, C93: 39pF C0G; C_0402_1005Metric
C87, C88: 1.8pF C0G; C_0402_1005Metric
C89: 2.4pF C0G; C_0402_1005Metric
C92, C94: 3.3pF C0G; C_0402_1005Metric
FL1: MLPF-WB55-01E3; FILTER-SMD_6P-L1.6-W1.0-P0.50-BL; LCSC Part C2651048
L1: 10uH; L_0603_1608Metric
L2: 10nH; L_0603_1608Metric
L4: LQW15AN15NG00D; IND-SMD_L1.0-W0.5-2; MPN LQW15AN15NG00D; LCSC Part C98055
L7: BLM15AX601SN1D; L0402; MPN BLM15AX601SN1D; LCSC Part C76886
L8: MLZ2012M150WT000; L0805; MPN MLZ2012M150WT000; LCSC Part C383402
L9: LQW15AN47NJ00D; L0402; MPN LQW15AN47NJ00D; LCSC Part C192855
L10: LQW15AN2N5B00D; L0402; MPN LQW15AN2N5B00D; LCSC Part C237342
L11: LQW15AN4N7C00D; L0402; MPN LQW15AN4N7C00D; LCSC Part C167480
L12: LQW15AN9N1G00D; L0402; MPN LQW15AN9N1G00D; LCSC Part C113122
R38, R42: 100R; R_0402_1005Metric
R41: 0K; R_0402_1005Metric
RF1: BWSMA-KWE-Z001; SMA-TH_BWSMA-KWE-Z001; LCSC Part C496551
TP1, TP2, TP3: TestPoint; TestPoint_Pad_1.0x1.0mm
U8: BMP581; LGA-10_L2.0-W2.0-P0.50-TL_BMP581; LCSC Part C5362283
U10: STM32WB55RGVx; QFN-68-1EP_8x8mm_P0.4mm_EP6.4x6.4mm; LCSC C401505
U11: SX1262IMLTRT; QFN-24-1EP_4x4mm_P0.5mm_EP2.6x2.6mm
U15: PE4259-63; SC-70-6_L2.2-W1.3-P0.65-LS2.1-BL; MPN PE4259-63; LCSC Part C470892
U17: NX2012SA-32.768KHZ-STD-MUB-2; CRYSTAL-SMD_L2.0-W1.2; LCSC Part C891748
X1, X4: NX2016SA-32MHZ-STD-CZS-5; OSC-SMD_4P-L2.0-W1.6-BL; LCSC Part C843260

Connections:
+3.3V: C5.1, C6.1, C8.1, C9.1, C10.1, C11.1, C12.1, C13.1, C14.1, C15.1, C16.1, C17.1, C79.1, C80.1, C95.2, C96.2, L7.2, U8.1 (VDDIO), U8.10 (VDD), U10.1 (VBAT), U10.13 (VREF+), U10.30 (VDD), U10.33 (VDDRF), U10.44 (VDDSMPS), U10.45 (VDD), U10.55 (VDDUSB), U10.68 (VDD), U11.1 (VDD_IN), U11.10 (VBAT), U11.11 (VBAT_IO); also elsewhere on the board
/MPU/MPU_RX: U10.66 (PB6); also elsewhere on the board
/MPU/MPU_TX: U10.67 (PB7); also elsewhere on the board
/TPU/BARO_CS: U8.6 (CSB), U10.46 (PB12)
/TPU/BARO_INT: U8.7 (INT), U10.50 (PC6)
/TPU/BARO_MISO: U8.5 (SDO), U10.48 (PB14)
/TPU/BARO_MOSI: U8.4 (SDI), U10.49 (PB15)
/TPU/BARO_SCK: U8.2 (SCK), U10.47 (PB13)
/TPU/LORA_BUSY: U11.14 (BUSY)
/TPU/LORA_CS: U11.19 (NSS)
/TPU/LORA_DIO1: U11.13 (DIO1)
/TPU/LORA_DIO2: R42.1, U11.12 (DIO2)
/TPU/LORA_DIO3: U11.6 (DIO3)
/TPU/LORA_MISO: U11.16 (MISO)
/TPU/LORA_MOSI: U11.17 (MOSI)
/TPU/LORA_RESET: U11.15 (~RESET)
/TPU/LORA_SCK: U11.18 (SCK)
/TPU/LORA_SW: R38.1
/TPU/LORA_XIN: C77.1, U11.3 (XTA), X4.1
/TPU/LORA_XOUT: C78.1, U11.4 (XTB), X4.3
/TPU/RF: FL1.3 (IN), U10.31 (RF1)
/TPU/TPU_HXIN: C2.1, U10.35 (OSC_IN), X1.1
/TPU/TPU_HXOUT: C3.1, U10.34 (OSC_OUT), X1.3
/TPU/TPU_LXIN: C4.1, U10.3 (PC14), U17.1 (OSC1)
/TPU/TPU_LXOUT: C18.1, U10.4 (PC15), U17.2 (OSC2)
/TPU/TPU_SWCLK: TP2.1 (1_1), U10.56 (PA14)
/TPU/TPU_SWDIO: TP1.1 (1_1), U10.54 (PA13)
BOOT_TPU: U10.5 (PH3); also elsewhere on the board
GND: C2.2, C3.2, C4.2, C5.2, C6.2, C7.2, C8.2, C9.2, C10.2, C11.2, C12.2, C13.2, C14.2, C15.2, C16.2, C17.2, C18.2, C77.2, C78.2, C79.2, C80.2, C81.2, C82.2, C83.2, C85.2, C87.2, C88.2, C90.2, C91.2, C92.2, C94.2, C95.1, C96.1, FL1.2 (GND4), FL1.4 (GND1), FL1.5 (GND2), FL1.6 (GND3), RF1.1, RF1.2, RF1.3, RF1.4, TP3.1 (1_1), U8.3 (VSS), U8.8 (VSS), U8.9 (VSS), U10.32 (VSSRF), U10.42 (VSSSMPS), U10.69 (VSS), U11.2 (GND), U11.5 (GND), U11.8 (GND), U11.20 (GND), U11.25 (GND), U15.2 (GND), X1.2 (GND), X1.4 (GND), X4.2 (GND), X4.4 (GND); also elsewhere on the board
unnamed: AE1.1 (ANT_1), FL1.1 (OUT)
unnamed: C84.1, L9.2, L10.1, R41.2
unnamed: C84.2, C85.1, C86.1, L10.2
unnamed: C86.2, L11.1
unnamed: C92.1, C93.2, L12.1
unnamed: C94.1, L12.2, RF1.5
unnamed: L1.1, L2.2
unnamed: C7.1, L1.2, U10.41 (VFBSMPS)
unnamed: L2.1, U10.43 (VLXSMPS)
unnamed: L8.1, U11.9 (DCC_SW)
unnamed: C89.1, L4.1, U11.22 (RFI_N)
unnamed: C88.1, L4.2, U11.21 (RFI_P)
unnamed: R41.1, U11.23 (RFO)
unnamed: C81.1, L8.2, U11.7 (VREG)
unnamed: C82.1, C83.1, L9.1, U11.24 (VR_PA)
unnamed: C90.1, R38.2, U15.6 (CTRL#orVDD)
unnamed: C91.1, R42.2, U15.4 (CTRL)
unnamed: C87.1, L11.2, U15.1 (RF1)
unnamed: C89.2, U15.3 (RF2)
unnamed: C93.1, U15.5 (RFC)
RESET_TPU: U10.8 (NRST); also elsewhere on the board
TPU_B: U10.17 (PA2); also elsewhere on the board
TPU_DN: U10.52 (PA11); also elsewhere on the board
TPU_DP: U10.53 (PA12); also elsewhere on the board
TPU_G: U10.16 (PA1); also elsewhere on the board
TPU_R: U10.15 (PA0); also elsewhere on the board
TPU_VDDA: L7.1, U10.14 (VDDA)
